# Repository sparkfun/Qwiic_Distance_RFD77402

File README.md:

Qwiic Distance Sensor - RFD77402
========================================

[*Distance Sensor-RFD77402 (SEN-14539)*](https://www.sparkfun.com/products/14539)

The Qwiic Distance Sensor uses the RFD77402 sensor utilizing VCSEL or vertical-cavity surface-emitting laser and a 3 pixel camera to measure the amount of time to a target. This gives you amazing millimeter prescision with low-cost and low power.

Documentation
--------------
* **[Library](https://github.com/sparkfun/SparkFun_RFD77402_Arduino_Library)** - Arduino library for the RFD77402 Breakout Board.
* **[Hookup Guide](https://learn.sparkfun.com/tutorials/qwiic-distance-sensor-rfd77402-hookup-guide)** - Basic hookup guide for the RFD77402 Breakout Board.
* **[Qwiic System](http://www.sparkfun.com/qwiic)** - The Qwiic system enables fast and solderless connection between popular platforms and various sensors and actuators.

Product Versions
----------------
* [SEN-14539](https://www.sparkfun.com/products/14539)
* [SPX-14343](https://www.sparkfun.com/products/14343)

License Information
-------------------

This product is _**open source**_!

Please review the LICENSE.md file for license information.

If you have any questions or concerns on licensing, please contact techsupport@sparkfun.com.

Distributed as-is; no warranty is given.

- Your friends at SparkFun.

_<COLLABORATION CREDIT>_

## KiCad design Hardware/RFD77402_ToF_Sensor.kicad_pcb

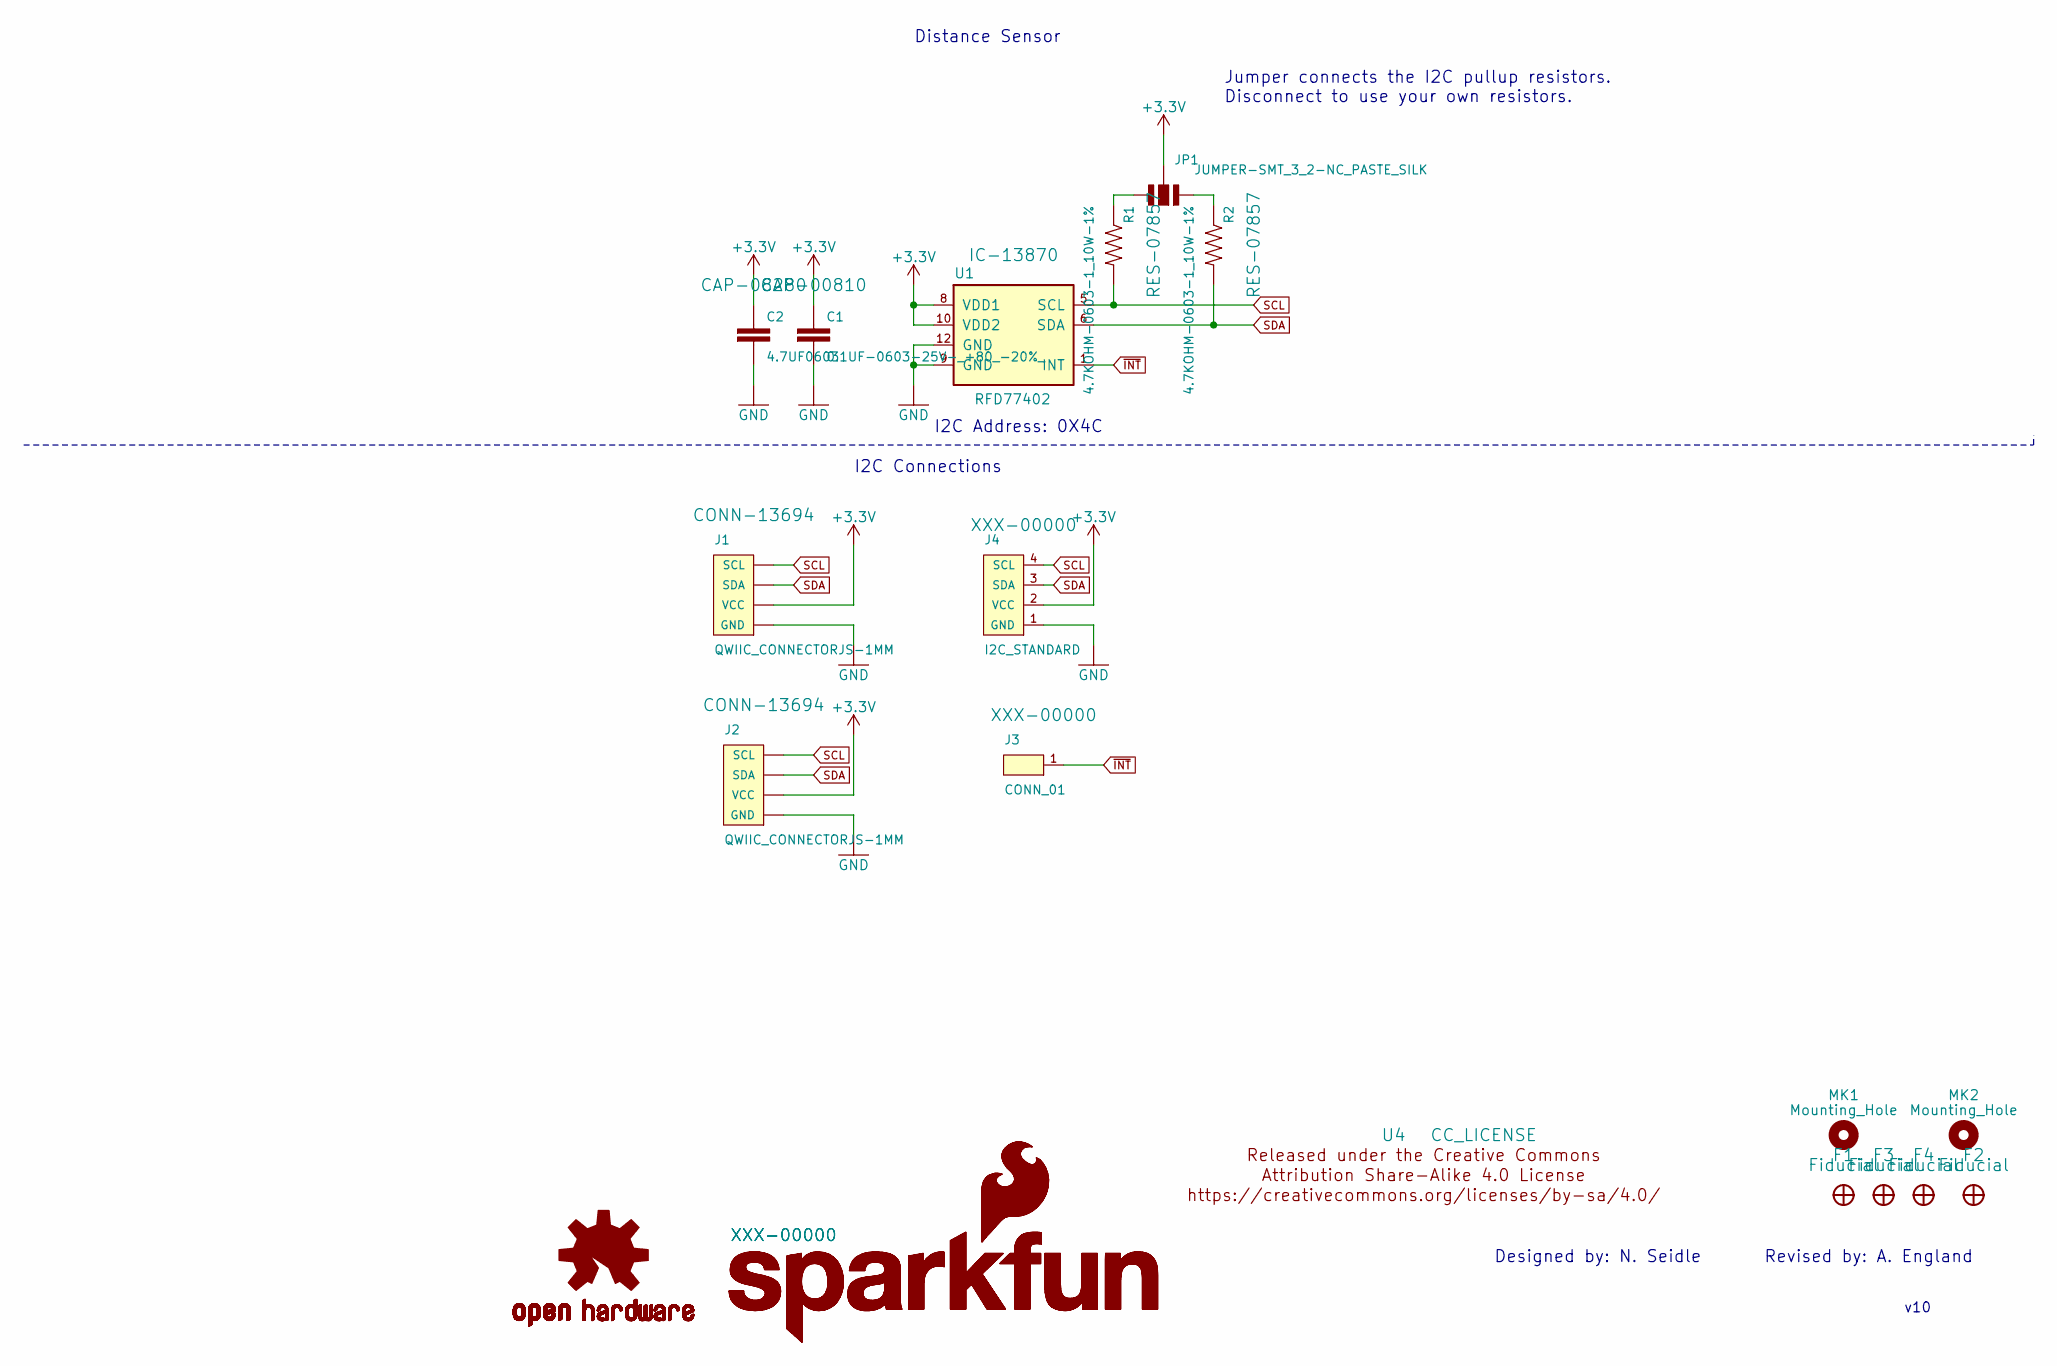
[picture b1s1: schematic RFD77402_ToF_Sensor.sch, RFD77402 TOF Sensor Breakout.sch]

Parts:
C1: 0.1UF-0603-25V-_+80_-20%_; 0603
C2: 4.7UF0603; 0603
F1, F2, F3, F4: Fiducial; FIDUCIAL-MICRO-NO_PASTE
J1, J2: QWIIC_CONNECTORJS-1MM; 1X04_1MM_RA
J3: CONN_01; 1X01
J4: I2C_STANDARD; 1X04
JP1: JUMPER-SMT_3_2-NC_PASTE_SILK; SMT-JUMPER_3_2-NC_PASTE_SILK
LOGO1: SPARKFUN-AESTHETICS_OSHW-LOGOS; OSHW-LOGO-MINI
LOGO2, LOGO3: SFE_LOGO_NAME_FLAME.1_INCH; SFE_LOGO_NAME_FLAME_.1
MK1, MK2: Mounting_Hole; STAND-OFF
R1, R2: 4.7KOHM-0603-1_10W-1%; 0603
U1: RFD77402
U4: CC_LICENSE; CREATIVE_COMMONS

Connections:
+3V3: C1.1, C2.1, J1.2 (VCC), J2.2 (VCC), J4.2 (VCC), JP1.2, U1.8 (VDD1), U1.10 (VDD2)
GND: C1.2, C2.2, J1.1 (GND), J2.1 (GND), J4.1 (GND), U1.9 (GND), U1.12 (GND)
unnamed: JP1.1, R2.1
unnamed: JP1.3, R1.1
SCL: J1.4 (SCL), J2.4 (SCL), J4.4 (SCL), R1.2, U1.5 (SCL)
SDA: J1.3 (SDA), J2.3 (SDA), J4.3 (SDA), R2.2, U1.6 (SDA)
~INT: J3.1, U1.1 (INT)

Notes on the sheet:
v10
Distance Sensor
I2C Connections
Jumper connects the I2C pullup resistors. Disconnect to use your own resistors.
I2C Address: 0X4C
Designed by: N. Seidle
Revised by: A. England

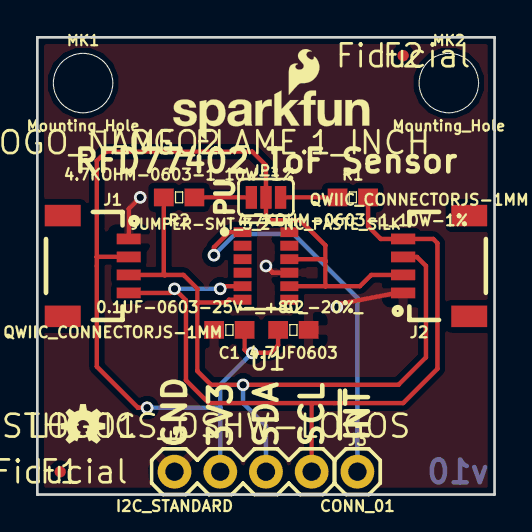
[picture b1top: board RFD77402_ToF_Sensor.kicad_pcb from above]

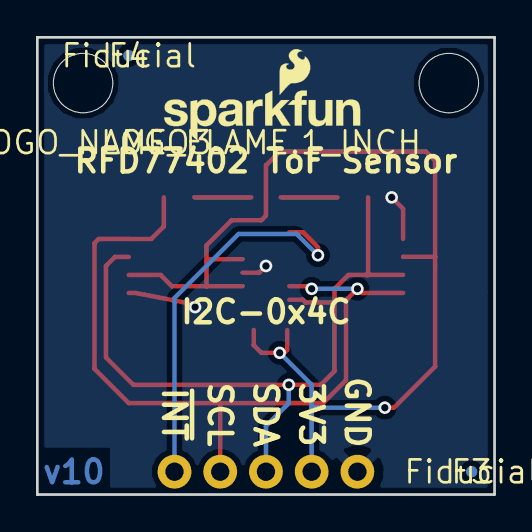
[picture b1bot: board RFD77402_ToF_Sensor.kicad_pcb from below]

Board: 2 copper layers, 25.4 x 25.4 mm, 20 parts (3 on the bottom side), 7 nets.

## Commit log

2017-11-15 Changed board silk
2017-11-17 Added fiducials
2017-11-21 Post design review changes
2017-11-28 Post checklist changes
2018-01-11 fixed paste issue with fiducial
2018-01-12 panel

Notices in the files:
parts and their libraries:
Released under the Creative Commons Attribution Share-Alike 4.0 License
https://creativecommons.org/licenses/by-sa/4.0
